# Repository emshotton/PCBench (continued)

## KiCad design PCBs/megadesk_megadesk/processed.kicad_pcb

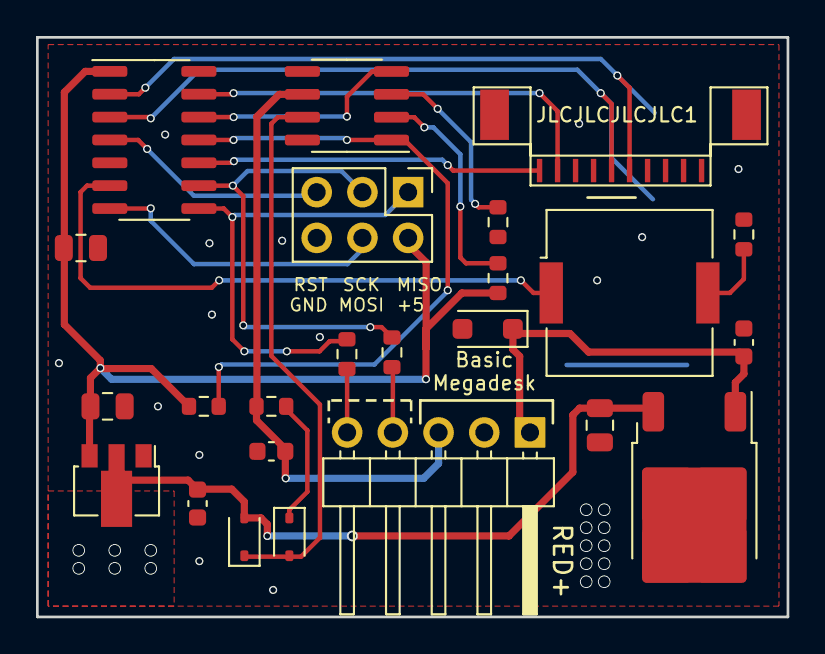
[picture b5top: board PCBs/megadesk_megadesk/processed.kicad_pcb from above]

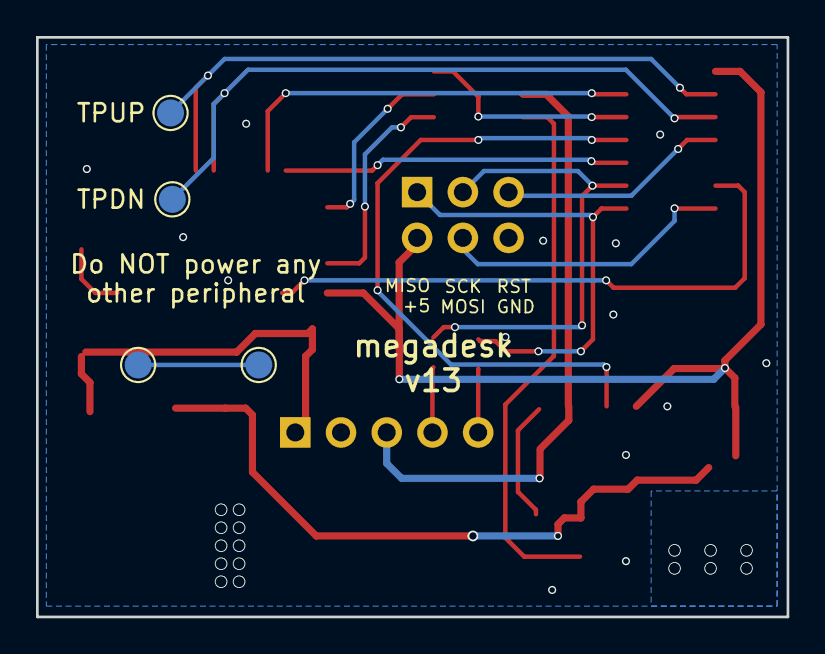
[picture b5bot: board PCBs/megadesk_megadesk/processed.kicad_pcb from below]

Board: 2 copper layers, 41.7 x 32.2 mm, 28 parts (4 on the bottom side), 24 nets.

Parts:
BZ1: Buzzer; Buzzer_Murata_PKMCS0909E
C1, C2, C6: 220pF; C_0603_1608Metric
C3, C4, C5: 0.1uF; C_0805_2012Metric
D1, D2: 1N4148; D_SOD-323
D3: SMF33A; D_SOD-123F
J2: FFC; F1004-H-10-20G-R
J3: AVR-ISP-6; PinHeader_2x03_P2.54mm_Vertical
J4: Interface; PinHeader_1x05_P2.54mm_Horizontal
R1, R2, R6, R7: 1k; R_0603_1608Metric
R3, R4, R5: 4.7k; R_0603_1608Metric
TP1, TP2: TestPoint; TestPoint_Pad_D1.5mm
TP3: TPDN; TestPoint_Pad_D1.5mm
TP4: TPUP; TestPoint_Pad_D1.5mm
U1: 7812; TO-252-2
U2: HT7550-1; SOT-89-3
U3: ATtiny841-SS; SOIC-14_3.9x8.7mm_P1.27mm
U4: MCP2003B; SOIC-8_3.9x4.9mm_P1.27mm

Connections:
+5V: C4.1, C5.1, J3.2 (VCC), R3.1, R4.2, U2.3 (VO), U3.1 (VCC)
+12V: C2.1, C3.1, D1.2 (A), U1.3 (OUT), U2.2 (VI)
+24V: C1.1, D3.1 (K), J4.1, U1.1 (IN)
/AVRRX: J4.4, R2.2
/AVRTX: J4.5, R7.2
/MISO: J3.1 (MISO), R7.1, U3.8 (PA5)
/MOSI: J3.4 (MOSI), U3.7 (PA6)
/RST: J3.5 (~RST), U3.4 (~RESET/PB3)
/SCK: J3.3 (SCK), R2.1, U3.9 (PA4)
B9: J2.9, U3.13 (AREF/PA0)
B10: J2.10, U3.10 (PA3)
Bdown: J2.6, TP3.1, U3.3 (XTAL2/PB1)
Bup: J2.5, TP4.1, U3.2 (XTAL1/PB0)
GND: C1.2, C2.2, C3.2, C4.2, C5.2, C6.2, D3.2 (A), J2.7, J3.6 (GND), J4.2, R1.2, R5.2, U1.2 (GND), U2.1 (GND), U3.14 (GND), U4.5 (VSS)
LINBUS: C6.1, J4.3, R6.2, U4.6 (LBUS)
unnamed: BZ1.2 (+), R1.1
unnamed: BZ1.1 (-), U3.6 (PA7)
unnamed: D1.1 (K), D2.2 (A), U4.7 (VBB)
unnamed: D2.1 (K), R6.1
unnamed: TP1.1, TP2.1
unnamed: U3.12 (PA1), U4.4 (TXD)
unnamed: R3.2, U3.11 (PA2), U4.1 (RXD)
unnamed: R4.1, U4.2 (CS)
unnamed: R5.1, U4.3 (WAKE)

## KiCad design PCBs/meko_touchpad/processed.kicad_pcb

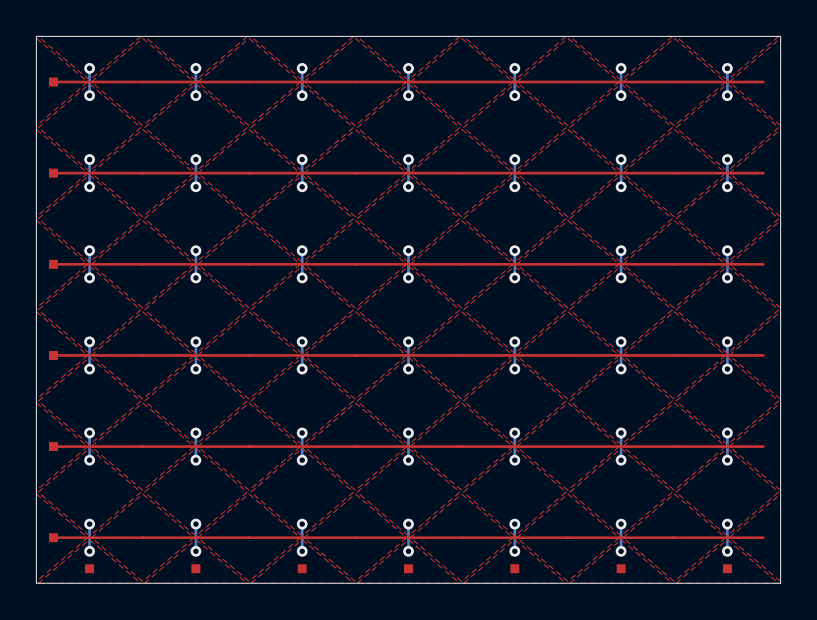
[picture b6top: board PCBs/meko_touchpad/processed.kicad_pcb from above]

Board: 2 copper layers, 41.3 x 30.4 mm, 14 parts (1 on the bottom side), 14 nets.

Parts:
COL1, COL2, COL3, COL4, COL5, COL6, COL7: TESTPOINTPAD_0_5MM; PAD_0_5MM
ROW1, ROW2, ROW3, ROW4, ROW5, ROW6: TESTPOINTPAD_0_5MM; PAD_0_5MM
U1: IQS7211E; QFN-20-1EP_3x3mm_P0.4mm_EP1.65x1.65mm

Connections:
/COL1: COL1.P1 (P1_P1), U1.11 (RX6/TX6)
/COL2: COL2.P1 (P1_P1), U1.10 (RX5/TX5)
/COL3: COL3.P1 (P1_P1), U1.9 (RX4/TX4)
/COL4: COL4.P1 (P1_P1), U1.8 (RX3/TX3)
/COL5: COL5.P1 (P1_P1), U1.7 (RX2/TX2)
/COL6: COL6.P1 (P1_P1), U1.6 (RX1/TX1)
/COL7: COL7.P1 (P1_P1), U1.5 (RX0/TX0)
/ROW1: ROW1.P1 (P1_P1), U1.17 (TX12)
/ROW2: ROW2.P1 (P1_P1), U1.16 (TX11)
/ROW3: ROW3.P1 (P1_P1), U1.15 (TX10)
/ROW4: ROW4.P1 (P1_P1), U1.14 (TX9)
/ROW5: ROW5.P1 (P1_P1), U1.13 (TX8)
/ROW6: ROW6.P1 (P1_P1), U1.12 (RX7/TX7)
GND: U1.3 (VSS), U1.21 (TAB)
